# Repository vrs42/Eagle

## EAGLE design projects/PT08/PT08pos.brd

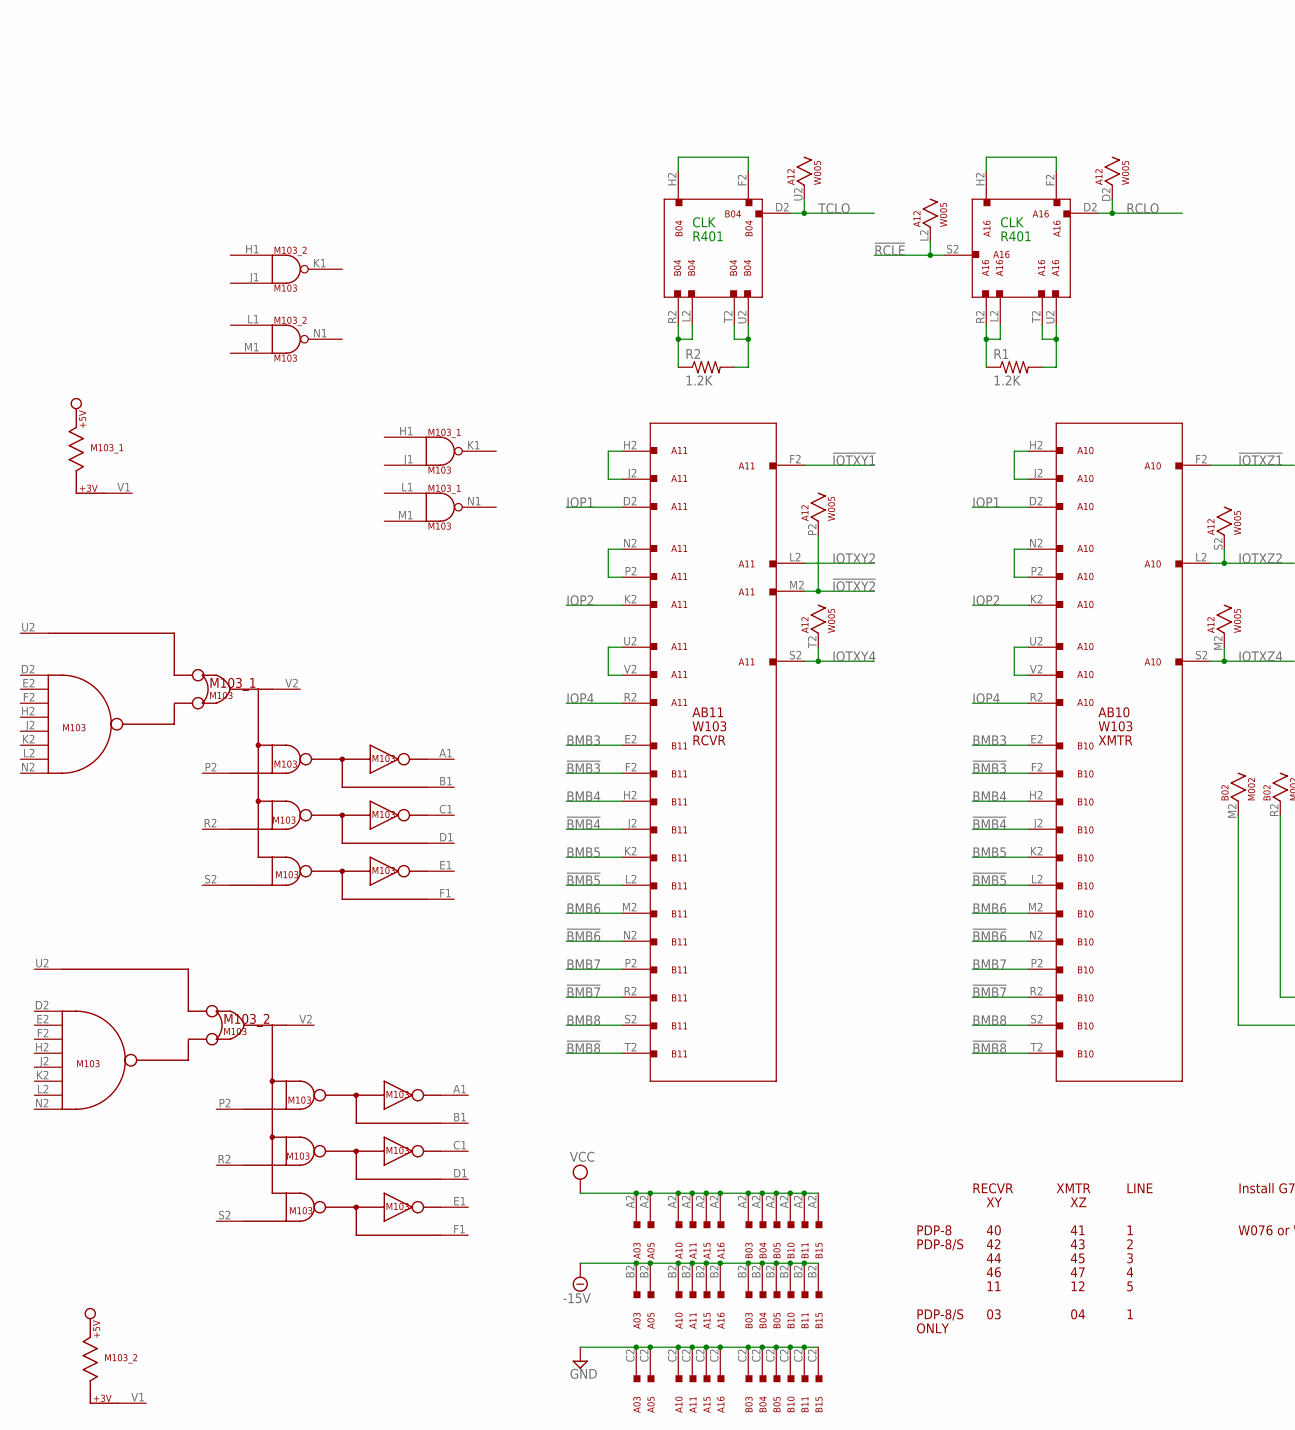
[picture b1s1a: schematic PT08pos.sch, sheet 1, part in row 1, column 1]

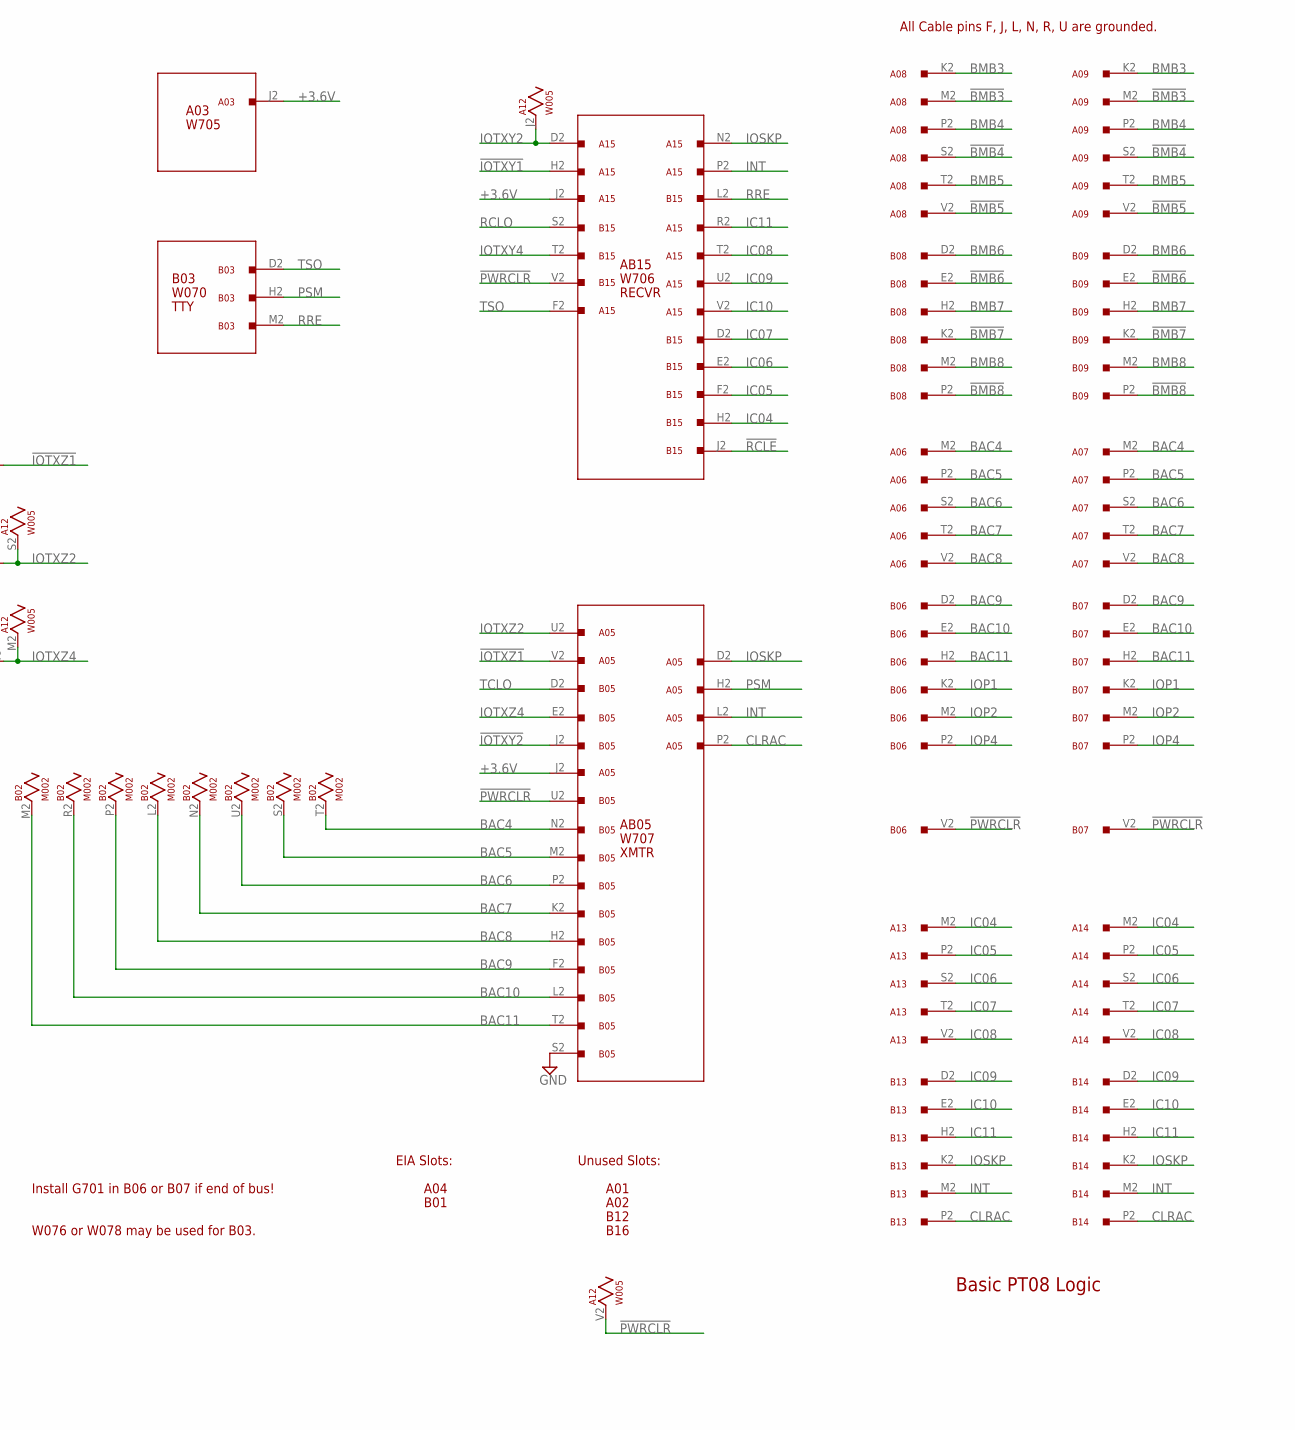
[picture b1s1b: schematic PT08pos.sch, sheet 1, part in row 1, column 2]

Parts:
A01, A02: H807
A03: W705; H807
A05: W707; H807
A06, A07, A08, A09, A13, A14: W011; H807
A10, A11: W103; H807
A12: W005; H807
A15: W706; H807
A16: R401; H807
B02: M002; H807
B03: W076; H807
B04: R401; H807
B05: W707; H807
B06, B07, B08, B09, B13, B14: W011; H807
B10, B11: W103; H807
B12, B16: H807
B15: W706; H807
M103_1, M103_2: M103; H807
R1, R2: 1.2K; 0207/10

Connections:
!BMB3: A08.M2, A09.M2, B10.F2, B11.F2
!BMB4: A08.S2, A09.S2, B10.J2, B11.J2
!BMB5: A08.V2, A09.V2, B10.L2, B11.L2
!BMB6: B08.E2, B09.E2, B10.N2, B11.N2
!BMB7: B08.K2, B09.K2, B10.R2, B11.R2
!BMB8: B08.P2, B09.P2, B10.T2, B11.T2
!IOTXY1: A11.F2, A15.H2
!IOTXY2: A11.M2, A12.P2, B05.J2
!IOTXZ1: A05.V2, A10.F2
!PWRCLR: A12.V2, B05.U2, B06.V2, B07.V2, B15.V2
!RCLE: A12.L2, A16.S2, B15.J2
+3.6V: A03.J2, A05.J2, A15.J2
-15V: A03.B2, A05.B2, A10.B2, A11.B2, A12.B2 (-15V), A15.B2, A16.B2, B03.B2, B04.B2, B05.B2, B10.B2, B11.B2, B15.B2; also elsewhere on the board
BAC4: A06.M2, A07.M2, B02.T2, B05.N2
BAC5: A06.P2, A07.P2, B02.S2, B05.M2
BAC6: A06.S2, A07.S2, B02.U2, B05.P2
BAC7: A06.T2, A07.T2, B02.N2, B05.K2
BAC8: A06.V2, A07.V2, B02.L2, B05.H2
BAC9: B02.P2, B05.F2, B06.D2, B07.D2
BAC10: B02.R2, B05.L2, B06.E2, B07.E2
BAC11: B02.M2, B05.T2, B06.H2, B07.H2
BMB3: A08.K2, A09.K2, B10.E2, B11.E2
BMB4: A08.P2, A09.P2, B10.H2, B11.H2
BMB5: A08.T2, A09.T2, B10.K2, B11.K2
BMB6: B08.D2, B09.D2, B10.M2, B11.M2
BMB7: B08.H2, B09.H2, B10.P2, B11.P2
BMB8: B08.M2, B09.M2, B10.S2, B11.S2
CLRAC: A05.P2, B13.P2, B14.P2
GND: A03.C2, A05.C2, A06.C2 (GND), A06.F2 (GND), A06.J2 (GND), A06.L2 (GND), A06.N2 (GND), A06.R2 (GND), A06.U2 (GND), A07.C2 (GND), A07.F2 (GND), A07.J2 (GND), A07.L2 (GND), A07.N2 (GND), A07.R2 (GND), A07.U2 (GND), A08.C2 (GND), A08.F2 (GND), A08.J2 (GND), A08.L2 (GND), A08.N2 (GND), A08.R2 (GND), A08.U2 (GND), A09.C2 (GND), A09.F2 (GND), A09.J2 (GND), A09.L2 (GND), A09.N2 (GND), A09.R2 (GND), A09.U2 (GND), A10.C2, A11.C2, A12.C2 (GND), A13.C2 (GND), A13.F2 (GND), A13.J2 (GND), A13.L2 (GND), A13.N2 (GND), A13.R2 (GND), A13.U2 (GND), A14.C2 (GND), A14.F2 (GND), A14.J2 (GND), A14.L2 (GND), A14.N2 (GND), A14.R2 (GND), A14.U2 (GND), A15.C2, A16.C2, B02.C2 (GND), B03.C2, B04.C2, B05.C2, B05.S2, B06.C2 (GND), B06.F2 (GND), B06.J2 (GND), B06.L2 (GND), B06.N2 (GND), B06.R2 (GND), B06.U2 (GND), B07.C2 (GND), B07.F2 (GND), B07.J2 (GND), B07.L2 (GND), B07.N2 (GND), B07.R2 (GND), B07.U2 (GND), B08.C2 (GND), B08.F2 (GND), B08.J2 (GND), B08.L2 (GND), B08.N2 (GND), B08.R2 (GND), B08.U2 (GND), B09.C2 (GND), B09.F2 (GND), B09.J2 (GND), B09.L2 (GND), B09.N2 (GND), B09.R2 (GND), B09.U2 (GND), B10.C2, B11.C2, B13.C2 (GND), B13.F2 (GND), B13.J2 (GND), B13.L2 (GND), B13.N2 (GND), B13.R2 (GND), B13.U2 (GND), B14.C2 (GND), B14.F2 (GND), B14.J2 (GND), B14.L2 (GND), B14.N2 (GND), B14.R2 (GND), B14.U2 (GND), B15.C2, M103_1.C2 (GND), M103_1.T1 (GND), M103_2.C2 (GND), M103_2.T1 (GND); also elsewhere on the board
IC04: A13.M2, A14.M2, B15.H2
IC05: A13.P2, A14.P2, B15.F2
IC06: A13.S2, A14.S2, B15.E2
IC07: A13.T2, A14.T2, B15.D2
IC08: A13.V2, A14.V2, A15.T2
IC09: A15.U2, B13.D2, B14.D2
IC10: A15.V2, B13.E2, B14.E2
IC11: A15.R2, B13.H2, B14.H2
INT: A05.L2, A15.P2, B13.M2, B14.M2
IOP1: A10.D2, A11.D2, B06.K2, B07.K2
IOP2: A10.K2, A11.K2, B06.M2, B07.M2
IOP4: A10.R2, A11.R2, B06.P2, B07.P2
IOSKP: A05.D2, A15.N2, B13.K2, B14.K2
IOTXY2: A11.L2, A12.J2, A15.D2
IOTXY4: A11.S2, A12.T2, B15.T2
IOTXZ2: A05.U2, A10.L2, A12.S2
IOTXZ4: A10.S2, A12.M2, B05.E2
unnamed: A10.U2, A10.V2
unnamed: A16.F2, A16.H2
unnamed: A16.L2, A16.R2, R1.1
unnamed: A16.T2, A16.U2, R1.2
unnamed: A10.H2, A10.J2
unnamed: B04.F2, B04.H2
unnamed: B04.L2, B04.R2, R2.1
unnamed: B04.T2, B04.U2, R2.2
unnamed: A11.U2, A11.V2
unnamed: A11.H2, A11.J2
unnamed: A10.N2, A10.P2
unnamed: A11.N2, A11.P2
PSM: A05.H2, B03.H2; also elsewhere on the board
RCLO: A12.D2, A16.D2, B15.S2
RRE: B03.M2, B15.L2
TCLO: A12.U2, B04.D2, B05.D2
TSO: A15.F2, B03.D2; also elsewhere on the board
VCC: A03.A2, A05.A2, A10.A2, A11.A2, A12.A2 (VCC), A15.A2, A16.A2, B02.A2 (VCC), B03.A2, B04.A2, B05.A2, B10.A2, B11.A2, B15.A2, M103_1.A2 (VCC), M103_2.A2 (VCC); also elsewhere on the board

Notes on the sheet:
R401
CLK
AB11
RCVR
AB10
XMTR
AB05
W707
W103
W705
A03
AB15
RECVR
W706
B03
W070
TTY
Unused Slots:
Basic PT08 Logic
LINE
PDP-8
PDP-8/S
ONLY
Install G701 in B06 or B07 if end of bus!
All Cable pins F, J, L, N, R, U are grounded.
W076 or W078 may be used for B03.
EIA Slots:
B01
A04

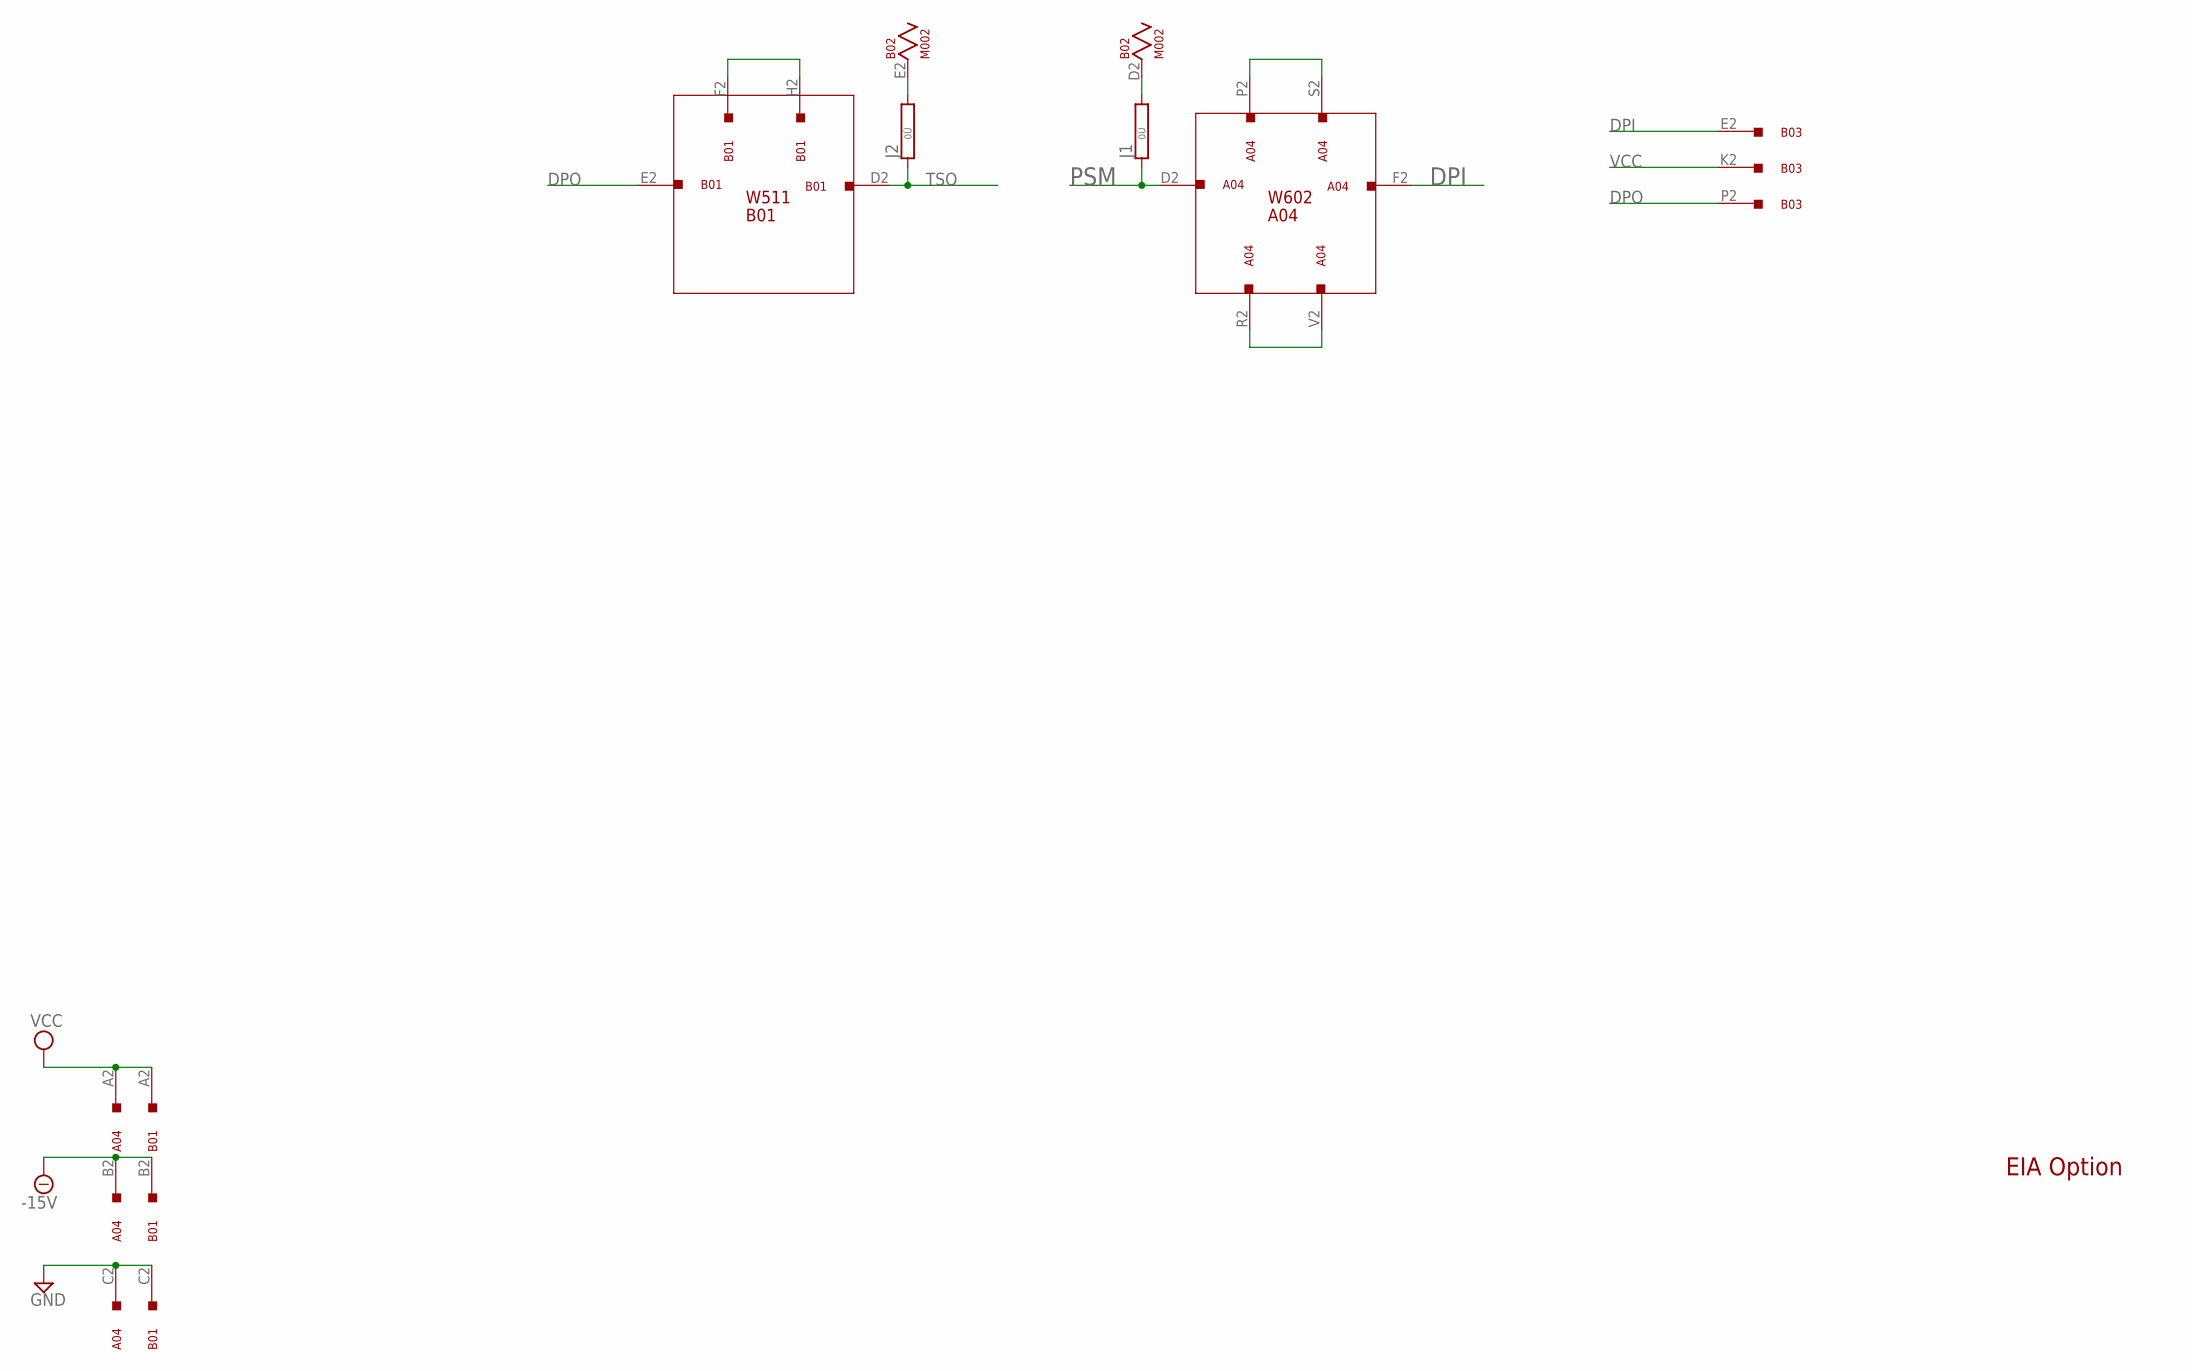
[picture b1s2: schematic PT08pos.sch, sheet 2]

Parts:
A04: W602; H807
B01: W511; H807
B02: M002; H807
B03: W076; H807
J1, J2: 0R; 0R/10

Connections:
-15V: A04.B2, B01.B2; also elsewhere on the board
DPI: A04.F2, B03.E2
DPO: B01.E2, B03.P2
GND: A04.C2, B01.C2, B02.C2 (GND); also elsewhere on the board
unnamed: A04.P2, A04.S2
unnamed: A04.R2, A04.V2
unnamed: B02.D2, J1.2
unnamed: B01.F2, B01.H2
unnamed: B02.E2, J2.2
PSM: A04.D2, J1.1; also elsewhere on the board
TSO: B01.D2, J2.1; also elsewhere on the board
VCC: A04.A2, B01.A2, B02.A2 (VCC), B03.K2; also elsewhere on the board

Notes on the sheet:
EIA Option
W602
A04
B01
W511

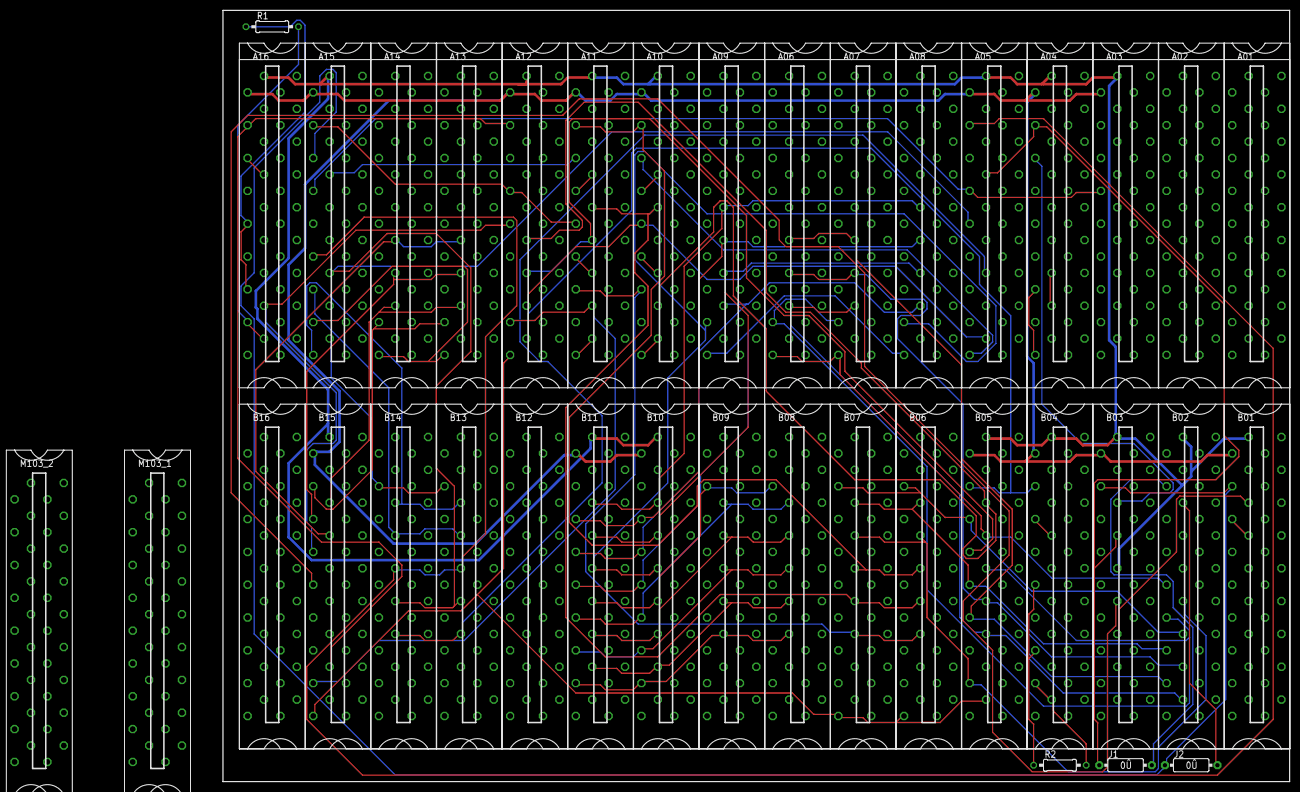
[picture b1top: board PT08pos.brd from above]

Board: 3 copper layers, 206.4 x 149.2 mm, 42 parts (0 on the bottom side), 71 nets.

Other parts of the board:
U$1, U$2, U$3, U$4: CBLOCK

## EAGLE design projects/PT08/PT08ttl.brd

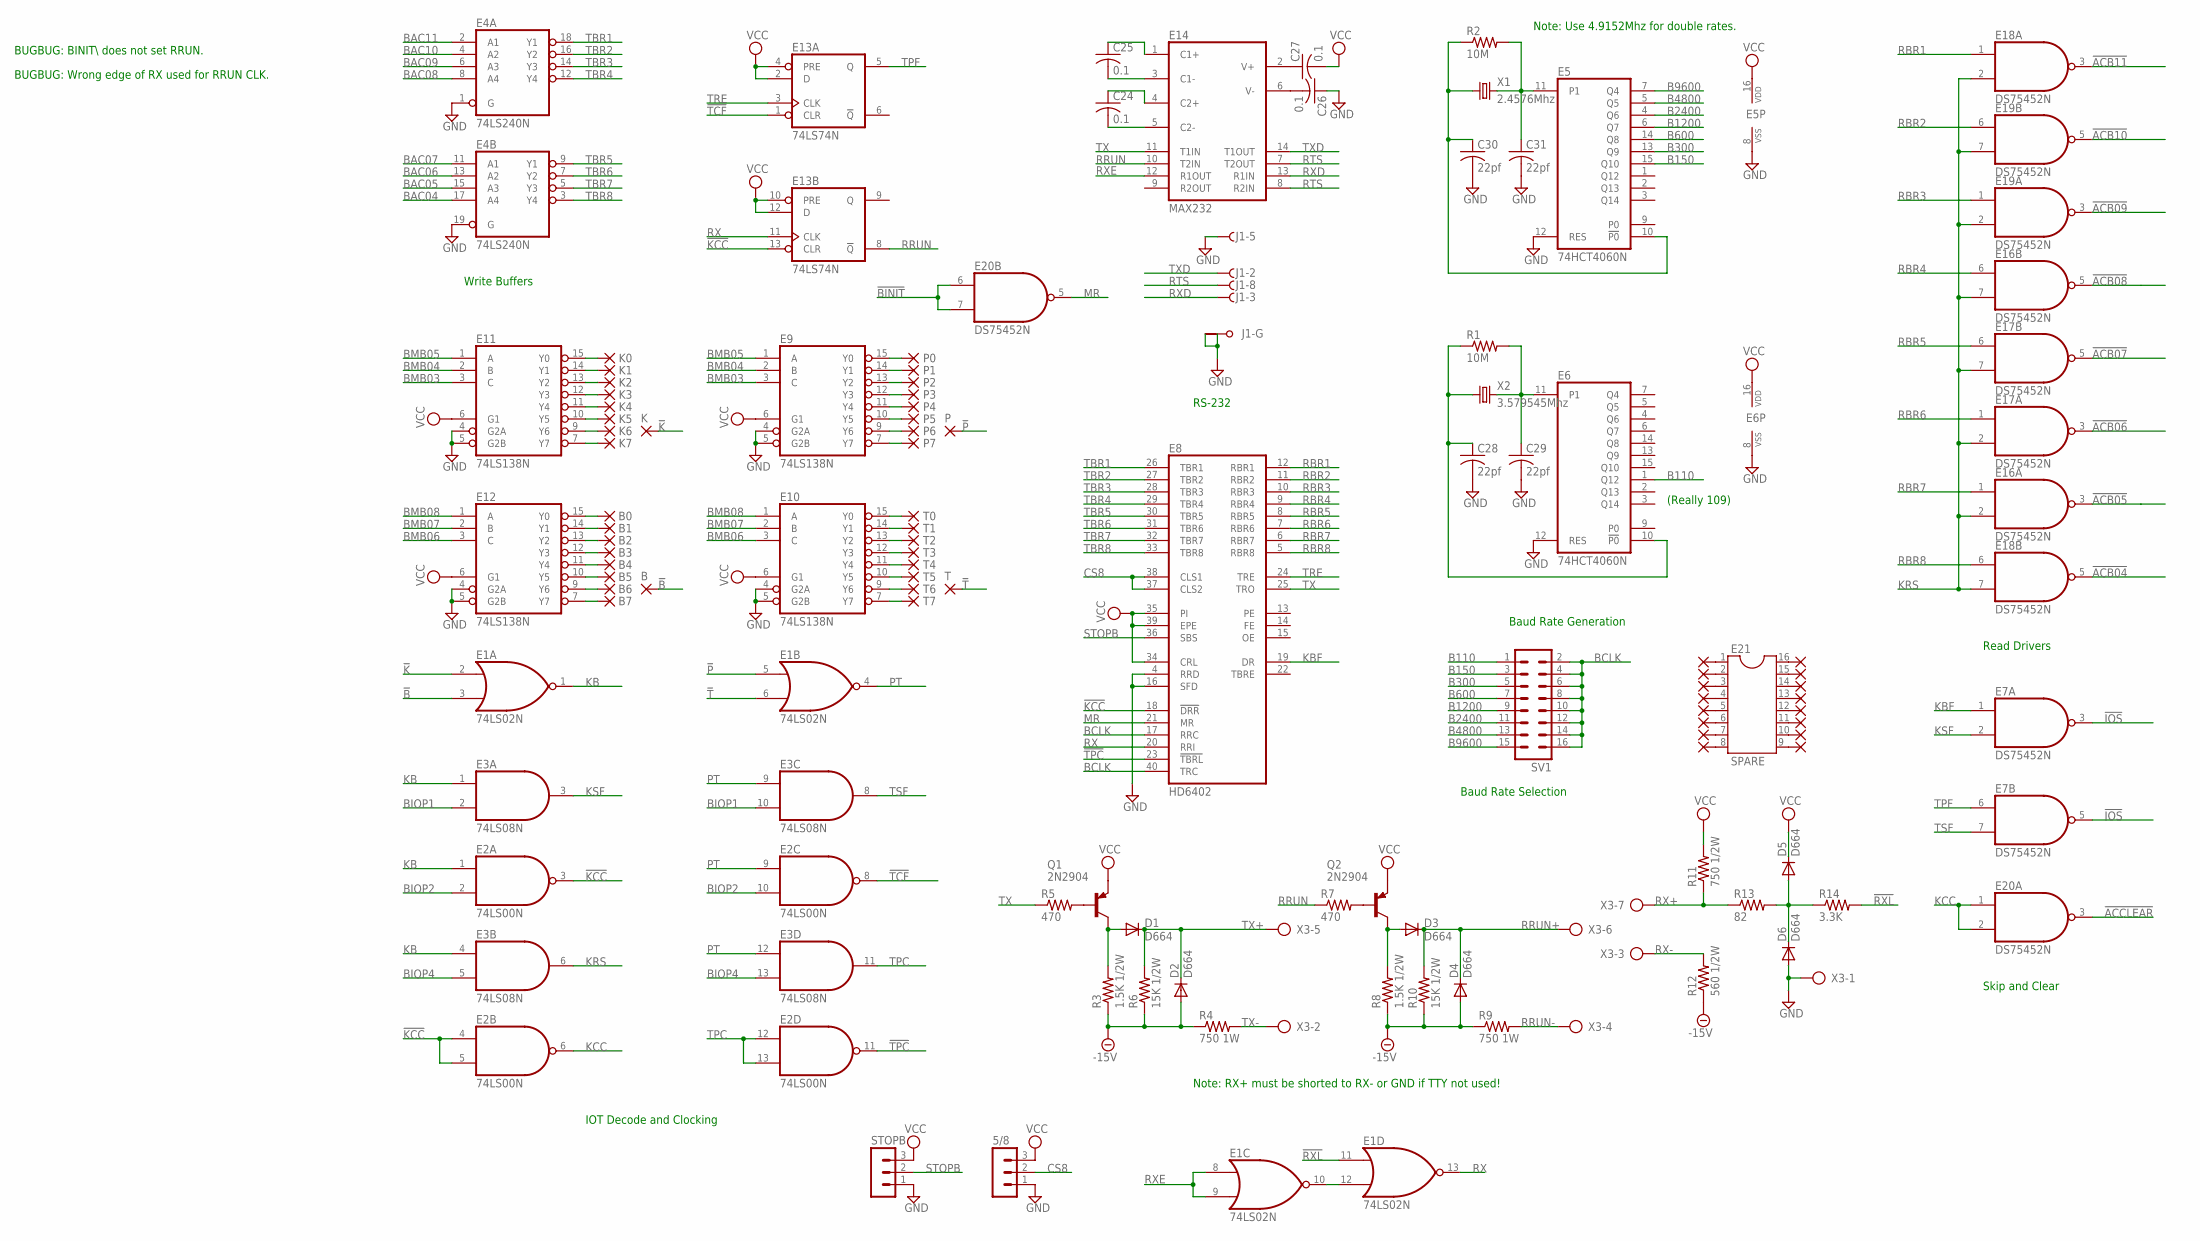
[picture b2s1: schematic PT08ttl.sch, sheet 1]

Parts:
5/8: MA03-1
B, B0, B1, B2, B3, B4, B5, B6, B7: 1,6/0,8
C24, C25, C26, C27: 0.1; C050-025X075
C28, C29, C30, C31: 22pf; C050-025X075
D1, D2, D3, D4, D5, D6: D664; DO35-10
E1: 74LS02N; DIL14
E2: 74LS00N; DIL14
E3: 74LS08N; DIL14
E4: 74LS240N; DIL20
E5, E6: 74HCT4060N; DIL16
E7, E16, E17, E18, E19, E20: DS75452N; DIL08
E8: HD6402; DIL40
E9, E10, E11, E12: 74LS138N; DIL16
E13: 74LS74N; DIL14
E14: MAX232; DIL16
E21: SPARE; DIL16
J1: F09HPS; F09HP
K, K0, K1, K2, K3, K4, K5, K6, K7: 1,6/0,8
P, P0, P1, P2, P3, P4, P5, P6, P7: 1,6/0,8
PAD18, PAD19, PAD28, PAD29, PAD30, PAD31, PAD32, PAD33, PAD34, PAD35, PAD36, PAD37, PAD38, PAD39, PAD40, PAD41: 1,6/0,8
Q1, Q2: 2N2904; TO39
R1, R2: 10M; 0207/10
R3, R8: 1.5K 1/2W; 0207/10
R4, R9: 750 1W; 0207/10
R5, R7: 470; 0207/10
R6, R10: 15K 1/2W; 0207/10
R11: 750 1/2W; 0207/10
R12: 560 1/2W; 0207/10
R13: 82; 0207/10
R14: 3.3K; 0207/10
STOPB: MA03-1
SV1: MA08-2
T, T0, T1, T2, T3, T4, T5, T6, T7: 1,6/0,8
X1: 2.4576Mhz; HC49U-V
X2: 3.579545Mhz; HC49U-V
X3: AK300/7

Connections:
!ACB04: E18.5 (O); also elsewhere on the board
!ACB05: E16.3 (O); also elsewhere on the board
!ACB06: E17.3 (O); also elsewhere on the board
!ACB07: E17.5 (O); also elsewhere on the board
!ACB08: E16.5 (O); also elsewhere on the board
!ACB09: E19.3 (O); also elsewhere on the board
!ACB10: E19.5 (O); also elsewhere on the board
!ACB11: E18.3 (O); also elsewhere on the board
!ACCLEAR: E20.3 (O); also elsewhere on the board
!B: B.1, E1.3 (I1)
!BINIT: E20.6 (I0), E20.7 (I1); also elsewhere on the board
!IOS: E7.3 (O), E7.5 (O); also elsewhere on the board
!K: E1.2 (I0), K.1
!KCC: E2.3 (O), E2.4 (I0), E2.5 (I1), E8.18 (!DRR), E13.13 (CLR)
!P: E1.5 (I0), P.1
!RXL: E1.11 (I0), R14.2
!T: E1.6 (I1), T.1
!TCF: E2.8 (O), E13.1 (CLR)
!TPC: E2.11 (O), E8.23 (!TBRL)
-15V: D2.A, D4.A, R3.1, R4.1, R6.1, R8.1, R9.1, R10.1, R12.1; also elsewhere on the board
B110: E6.1 (Q12), SV1.1
B150: E5.15 (Q10), SV1.3
B300: E5.13 (Q9), SV1.5
B600: E5.14 (Q8), SV1.7
B1200: E5.6 (Q7), SV1.9
B2400: E5.4 (Q6), SV1.11
B4800: E5.5 (Q5), SV1.13
B9600: E5.7 (Q4), SV1.15
BAC04: E4.17 (A4); also elsewhere on the board
BAC05: E4.15 (A3); also elsewhere on the board
BAC06: E4.13 (A2); also elsewhere on the board
BAC07: E4.11 (A1); also elsewhere on the board
BAC08: E4.8 (A4); also elsewhere on the board
BAC09: E4.6 (A3); also elsewhere on the board
BAC10: E4.4 (A2); also elsewhere on the board
BAC11: E4.2 (A1); also elsewhere on the board
BCLK: E8.17 (RRC), E8.40 (TRC), SV1.2, SV1.4, SV1.6, SV1.8, SV1.10, SV1.12, SV1.14, SV1.16
BIOP1: E3.2 (I1), E3.10 (I1); also elsewhere on the board
BIOP2: E2.2 (I1), E2.10 (I1); also elsewhere on the board
BIOP4: E3.5 (I1), E3.13 (I1); also elsewhere on the board
BMB03: E9.3 (C), E11.3 (C); also elsewhere on the board
BMB04: E9.2 (B), E11.2 (B); also elsewhere on the board
BMB05: E9.1 (A), E11.1 (A); also elsewhere on the board
BMB06: E10.3 (C), E12.3 (C); also elsewhere on the board
BMB07: E10.2 (B), E12.2 (B); also elsewhere on the board
BMB08: E10.1 (A), E12.1 (A); also elsewhere on the board
CS8: 5/8.2, E8.37 (CLS2), E8.38 (CLS1)
GND: 5/8.1, C26.1, C28.2, C29.2, C30.2, C31.2, D6.A, E1.7 (GND), E2.7 (GND), E3.7 (GND), E4.1 (G), E4.10 (GND), E4.19 (G), E5.8 (VSS), E5.12 (RES), E6.8 (VSS), E6.12 (RES), E7.4 (GND), E8.3 (GND), E8.4 (RRD), E8.16 (SFD), E9.4 (G2A), E9.5 (G2B), E9.8 (GND), E10.4 (G2A), E10.5 (G2B), E10.8 (GND), E11.4 (G2A), E11.5 (G2B), E11.8 (GND), E12.4 (G2A), E12.5 (G2B), E12.8 (GND), E13.7 (GND), E14.15 (GND), E16.4 (GND), E17.4 (GND), E18.4 (GND), E19.4 (GND), E20.4 (GND), J1.5 (F), J1.G1, J1.G2, STOPB.1, X3.1; also elsewhere on the board
KB: E1.1 (O), E2.1 (I0), E3.1 (I0), E3.4 (I0)
KBF: E7.1 (I0), E8.19 (DR)
KCC: E2.6 (O), E20.1 (I0), E20.2 (I1)
KRS: E3.6 (O), E16.2 (I1), E16.7 (I1), E17.2 (I1), E17.7 (I1), E18.2 (I1), E18.7 (I1), E19.2 (I1), E19.7 (I1)
KSF: E3.3 (O), E7.2 (I1)
MR: E8.21 (MR), E20.5 (O)
unnamed: B6.1, E12.9 (Y6)
unnamed: B0.1, E12.15 (Y0)
unnamed: B1.1, E12.14 (Y1)
unnamed: B2.1, E12.13 (Y2)
unnamed: B3.1, E12.12 (Y3)
unnamed: B4.1, E12.11 (Y4)
unnamed: B5.1, E12.10 (Y5)
unnamed: B7.1, E12.7 (Y7)
unnamed: C29.1, E6.11 (P1), R1.2, X2.2
unnamed: C28.1, E6.10 (!P0), R1.1, X2.1
unnamed: C26.2, E14.6 (V-)
unnamed: C27.1, E14.2 (V+)
unnamed: Q1.2 (B), R5.2
unnamed: D1.A, Q1.3 (C), R3.2
unnamed: Q2.2 (B), R7.2
unnamed: D3.A, Q2.3 (C), R8.2
unnamed: C24.2, E14.5 (C2-)
unnamed: C30.1, E5.10 (!P0), R2.1, X1.1
unnamed: D5.A, D6.C, R13.2, R14.1
unnamed: C31.1, E5.11 (P1), R2.2, X1.2
unnamed: E1.10 (O), E1.12 (I1)
unnamed: C25.2, E14.3 (C1-)
unnamed: E21.1, PAD18.1
unnamed: E21.2, PAD19.1
unnamed: E21.3, PAD28.1
unnamed: C24.1, E14.4 (C2+)
unnamed: C25.1, E14.1 (C1+)
unnamed: E10.15 (Y0), T0.1
unnamed: E21.4, PAD29.1
unnamed: E21.5, PAD30.1
unnamed: E21.6, PAD31.1
unnamed: E21.7, PAD32.1
unnamed: E21.8, PAD33.1
unnamed: E21.16, PAD34.1
unnamed: E21.15, PAD35.1
unnamed: E21.14, PAD36.1
unnamed: E21.13, PAD37.1
unnamed: E21.12, PAD38.1
unnamed: E21.11, PAD39.1
unnamed: E21.10, PAD40.1
unnamed: E21.9, PAD41.1
unnamed: E11.15 (Y0), K0.1
unnamed: E11.14 (Y1), K1.1
unnamed: E11.13 (Y2), K2.1
unnamed: E11.12 (Y3), K3.1
unnamed: E11.11 (Y4), K4.1
unnamed: E11.10 (Y5), K5.1
unnamed: E11.7 (Y7), K7.1
unnamed: E11.9 (Y6), K6.1
unnamed: E10.14 (Y1), T1.1
unnamed: E10.13 (Y2), T2.1
unnamed: E10.12 (Y3), T3.1
unnamed: E10.11 (Y4), T4.1
unnamed: E10.10 (Y5), T5.1
unnamed: E10.7 (Y7), T7.1
unnamed: E10.9 (Y6), T6.1
unnamed: E9.15 (Y0), P0.1
unnamed: E9.14 (Y1), P1.1
unnamed: E9.13 (Y2), P2.1
unnamed: E9.12 (Y3), P3.1
unnamed: E9.11 (Y4), P4.1
unnamed: E9.10 (Y5), P5.1
unnamed: E9.7 (Y7), P7.1
unnamed: E9.9 (Y6), P6.1
PT: E1.4 (O), E2.9 (I0), E3.9 (I0), E3.12 (I0)
RBR1: E8.12 (RBR1), E18.1 (I0)
RBR2: E8.11 (RBR2), E19.6 (I0)
RBR3: E8.10 (RBR3), E19.1 (I0)
RBR4: E8.9 (RBR4), E16.6 (I0)
RBR5: E8.8 (RBR5), E17.6 (I0)
RBR6: E8.7 (RBR6), E17.1 (I0)
RBR7: E8.6 (RBR7), E16.1 (I0)
RBR8: E8.5 (RBR8), E18.6 (I0)
RRUN: E13.8 (!Q), E14.10 (T2IN), R7.1
RRUN+: D3.C, D4.C, R10.2, X3.6
RRUN-: R9.2, X3.4
RTS: E14.7 (T2OUT), E14.8 (R2IN), J1.8 (F)
RX: E1.13 (O), E8.20 (RRI), E13.11 (CLK)
RX+: R11.1, R13.1, X3.7
RX-: R12.2, X3.3
RXD: E14.13 (R1IN), J1.3 (F)
RXE: E1.8 (I0), E1.9 (I1), E14.12 (R1OUT)
STOPB: E8.36 (SBS), STOPB.2
TBR1: E4.18 (Y1), E8.26 (TBR1)
TBR2: E4.16 (Y2), E8.27 (TBR2)
TBR3: E4.14 (Y3), E8.28 (TBR3)
TBR4: E4.12 (Y4), E8.29 (TBR4)
TBR5: E4.9 (Y1), E8.30 (TBR5)
TBR6: E4.7 (Y2), E8.31 (TBR6)
TBR7: E4.5 (Y3), E8.32 (TBR7)
TBR8: E4.3 (Y4), E8.33 (TBR8)
TPC: E2.12 (I0), E2.13 (I1), E3.11 (O)
TPF: E7.6 (I0), E13.5 (Q)
TRE: E8.24 (TRE), E13.3 (CLK)
TSF: E3.8 (O), E7.7 (I1)
TX: E8.25 (TRO), E14.11 (T1IN), R5.1
TX+: D1.C, D2.C, R6.2, X3.5
TX-: R4.2, X3.2
TXD: E14.14 (T1OUT), J1.2 (F)
VCC: 5/8.3, C27.2, D5.C, E1.14 (VCC), E2.14 (VCC), E3.14 (VCC), E4.20 (VCC), E5.16 (VDD), E6.16 (VDD), E7.8 (VCC), E8.1 (VCC), E8.34 (CRL), E8.35 (PI), E8.39 (EPE), E9.6 (G1), E9.16 (VCC), E10.6 (G1), E10.16 (VCC), E11.6 (G1), E11.16 (VCC), E12.6 (G1), E12.16 (VCC), E13.2 (D), E13.4 (PRE), E13.10 (PRE), E13.12 (D), E13.14 (VCC), E14.16 (VCC), E16.8 (VCC), E17.8 (VCC), E18.8 (VCC), E19.8 (VCC), E20.8 (VCC), Q1.1 (E), Q2.1 (E), R11.2, STOPB.3; also elsewhere on the board

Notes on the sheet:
IOT Decode and Clocking
Read Drivers
Skip and Clear
RS-232
Write Buffers
(Really 109)
Baud Rate Generation
Baud Rate Selection
Note: RX+ must be shorted to RX- or GND if TTY not used!
Note: Use 4.9152Mhz for double rates.
BUGBUG: BINIT\\ does not set RRUN.
BUGBUG: Wrong edge of RX used for RRUN CLK.

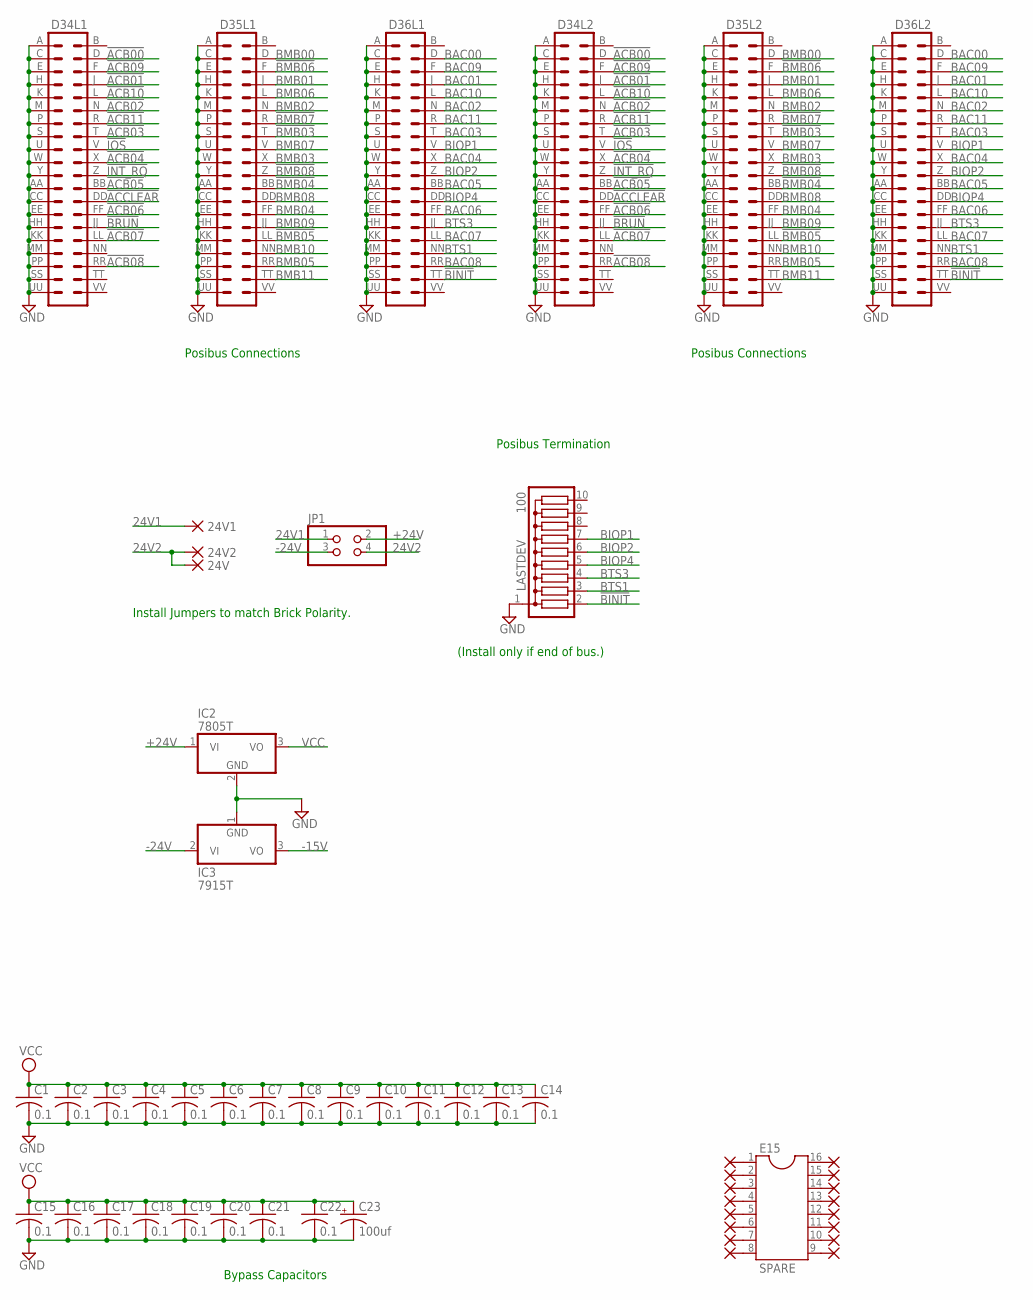
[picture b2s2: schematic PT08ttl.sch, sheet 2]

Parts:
24V, 24V1, 24V2: PAD-0820; 0820
C1, C2, C3, C4, C5, C6, C7, C8, C9, C10, C11, C12, C13, C14, C15, C16, C17, C18, C19, C20, C21, C22: 0.1; C050-025X075
C23: 100uf; E22-9
D34L1, D34L2, D35L1, D35L2, D36L1, D36L2: DEC40PINV
E15: SPARE; DIL16
IC2: 7805T; TO220H
IC3: 7915T; TO220H
JP1: PINHD-2X2; 2X02
LASTDEV: 100; SIL10
PAD1, PAD2, PAD3, PAD4, PAD5, PAD6, PAD7, PAD8, PAD9, PAD42, PAD43, PAD44, PAD45, PAD46, PAD47, PAD48: 1,6/0,8

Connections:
24V1: 24V1.P$1, JP1.1
24V2: 24V.P$1, 24V2.P$1, JP1.4
!ACB00: D34L1.D (4), D34L2.D (4)
!ACB01: D34L1.J (8), D34L2.J (8)
!ACB02: D34L1.N (12), D34L2.N (12)
!ACB03: D34L1.T (16), D34L2.T (16)
!ACB04: D34L1.X (20), D34L2.X (20); also elsewhere on the board
!ACB05: D34L1.BB (24), D34L2.BB (24); also elsewhere on the board
!ACB06: D34L1.FF (28), D34L2.FF (28); also elsewhere on the board
!ACB07: D34L1.LL (32), D34L2.LL (32); also elsewhere on the board
!ACB08: D34L1.RR (36), D34L2.RR (36); also elsewhere on the board
!ACB09: D34L1.F (6), D34L2.F (6); also elsewhere on the board
!ACB10: D34L1.L (10), D34L2.L (10); also elsewhere on the board
!ACB11: D34L1.R (14), D34L2.R (14); also elsewhere on the board
!ACCLEAR: D34L1.DD (26), D34L2.DD (26); also elsewhere on the board
!BINIT: D36L1.TT (38), D36L2.TT (38), LASTDEV.2; also elsewhere on the board
!BMB03: D35L1.T (16), D35L2.T (16)
!BMB04: D35L1.BB (24), D35L2.BB (24)
!BMB05: D35L1.LL (32), D35L2.LL (32)
!BMB06: D35L1.F (6), D35L2.F (6)
!BMB07: D35L1.R (14), D35L2.R (14)
!BMB08: D35L1.Z (22), D35L2.Z (22)
!BRUN: D34L1.JJ (30), D34L2.JJ (30)
!INT_RQ: D34L1.Z (22), D34L2.Z (22)
!IOS: D34L1.V (18), D34L2.V (18); also elsewhere on the board
+24V: IC2.1 (VI), JP1.2
-15V: IC3.3 (VO); also elsewhere on the board
-24V: IC3.2 (VI), JP1.3
BAC00: D36L1.D (4), D36L2.D (4)
BAC01: D36L1.J (8), D36L2.J (8)
BAC02: D36L1.N (12), D36L2.N (12)
BAC03: D36L1.T (16), D36L2.T (16)
BAC04: D36L1.X (20), D36L2.X (20); also elsewhere on the board
BAC05: D36L1.BB (24), D36L2.BB (24); also elsewhere on the board
BAC06: D36L1.FF (28), D36L2.FF (28); also elsewhere on the board
BAC07: D36L1.LL (32), D36L2.LL (32); also elsewhere on the board
BAC08: D36L1.RR (36), D36L2.RR (36); also elsewhere on the board
BAC09: D36L1.F (6), D36L2.F (6); also elsewhere on the board
BAC10: D36L1.L (10), D36L2.L (10); also elsewhere on the board
BAC11: D36L1.R (14), D36L2.R (14); also elsewhere on the board
BIOP1: D36L1.V (18), D36L2.V (18), LASTDEV.7; also elsewhere on the board
BIOP2: D36L1.Z (22), D36L2.Z (22), LASTDEV.6; also elsewhere on the board
BIOP4: D36L1.DD (26), D36L2.DD (26), LASTDEV.5; also elsewhere on the board
BMB00: D35L1.D (4), D35L2.D (4)
BMB01: D35L1.J (8), D35L2.J (8)
BMB02: D35L1.N (12), D35L2.N (12)
BMB03: D35L1.X (20), D35L2.X (20); also elsewhere on the board
BMB04: D35L1.FF (28), D35L2.FF (28); also elsewhere on the board
BMB05: D35L1.RR (36), D35L2.RR (36); also elsewhere on the board
BMB06: D35L1.L (10), D35L2.L (10); also elsewhere on the board
BMB07: D35L1.V (18), D35L2.V (18); also elsewhere on the board
BMB08: D35L1.DD (26), D35L2.DD (26); also elsewhere on the board
BMB09: D35L1.JJ (30), D35L2.JJ (30)
BMB10: D35L1.NN (34), D35L2.NN (34)
BMB11: D35L1.TT (38), D35L2.TT (38)
BTS1: D36L1.NN (34), D36L2.NN (34), LASTDEV.3
BTS3: D36L1.JJ (30), D36L2.JJ (30), LASTDEV.4
GND: C1.2, C2.2, C3.2, C4.2, C5.2, C6.2, C7.2, C8.2, C9.2, C10.2, C11.2, C12.2, C13.2, C14.2, C15.2, C16.2, C17.2, C18.2, C19.2, C20.2, C21.2, C22.2, C23.-, D34L1.A (1), D34L1.AA (23), D34L1.C (3), D34L1.CC (25), D34L1.E (5), D34L1.EE (27), D34L1.H (7), D34L1.HH (29), D34L1.K (9), D34L1.KK (31), D34L1.M (11), D34L1.MM (33), D34L1.P (13), D34L1.PP (35), D34L1.S (15), D34L1.SS (37), D34L1.U (17), D34L1.UU (39), D34L1.W (19), D34L1.Y (21), D34L2.A (1), D34L2.AA (23), D34L2.C (3), D34L2.CC (25), D34L2.E (5), D34L2.EE (27), D34L2.H (7), D34L2.HH (29), D34L2.K (9), D34L2.KK (31), D34L2.M (11), D34L2.MM (33), D34L2.P (13), D34L2.PP (35), D34L2.S (15), D34L2.SS (37), D34L2.U (17), D34L2.UU (39), D34L2.W (19), D34L2.Y (21), D35L1.A (1), D35L1.AA (23), D35L1.C (3), D35L1.CC (25), D35L1.E (5), D35L1.EE (27), D35L1.H (7), D35L1.HH (29), D35L1.K (9), D35L1.KK (31), D35L1.M (11), D35L1.MM (33), D35L1.P (13), D35L1.PP (35), D35L1.S (15), D35L1.SS (37), D35L1.U (17), D35L1.UU (39), D35L1.W (19), D35L1.Y (21), D35L2.A (1), D35L2.AA (23), D35L2.C (3), D35L2.CC (25), D35L2.E (5), D35L2.EE (27), D35L2.H (7), D35L2.HH (29), D35L2.K (9), D35L2.KK (31), D35L2.M (11), D35L2.MM (33), D35L2.P (13), D35L2.PP (35), D35L2.S (15), D35L2.SS (37), D35L2.U (17), D35L2.UU (39), D35L2.W (19), D35L2.Y (21), D36L1.A (1), D36L1.AA (23), D36L1.C (3), D36L1.CC (25), D36L1.E (5), D36L1.EE (27), D36L1.H (7), D36L1.HH (29), D36L1.K (9), D36L1.KK (31), D36L1.M (11), D36L1.MM (33), D36L1.P (13), D36L1.PP (35), D36L1.S (15), D36L1.SS (37), D36L1.U (17), D36L1.UU (39), D36L1.W (19), D36L1.Y (21), D36L2.A (1), D36L2.AA (23), D36L2.C (3), D36L2.CC (25), D36L2.E (5), D36L2.EE (27), D36L2.H (7), D36L2.HH (29), D36L2.K (9), D36L2.KK (31), D36L2.M (11), D36L2.MM (33), D36L2.P (13), D36L2.PP (35), D36L2.S (15), D36L2.SS (37), D36L2.U (17), D36L2.UU (39), D36L2.W (19), D36L2.Y (21), IC2.2 (GND), IC3.1 (GND), LASTDEV.1; also elsewhere on the board
unnamed: E15.1, PAD1.1
unnamed: E15.2, PAD2.1
unnamed: E15.3, PAD3.1
unnamed: E15.4, PAD4.1
unnamed: E15.5, PAD5.1
unnamed: E15.6, PAD6.1
unnamed: E15.7, PAD7.1
unnamed: E15.8, PAD8.1
unnamed: E15.16, PAD9.1
unnamed: E15.15, PAD42.1
unnamed: E15.14, PAD43.1
unnamed: E15.13, PAD44.1
unnamed: E15.12, PAD45.1
unnamed: E15.11, PAD46.1
unnamed: E15.10, PAD47.1
unnamed: E15.9, PAD48.1
VCC: C1.1, C2.1, C3.1, C4.1, C5.1, C6.1, C7.1, C8.1, C9.1, C10.1, C11.1, C12.1, C13.1, C14.1, C15.1, C16.1, C17.1, C18.1, C19.1, C20.1, C21.1, C22.1, C23.+, IC2.3 (VO); also elsewhere on the board

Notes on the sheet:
Bypass Capacitors
Posibus Connections
Posibus Termination
(Install only if end of bus.)
Install Jumpers to match Brick Polarity.
